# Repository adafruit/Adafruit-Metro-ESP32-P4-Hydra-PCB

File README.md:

# Adafruit-Metro-ESP32-P4-Hydra-PCB
PCB files for the Adafruit Metro ESP32-P4 Hydra - with 16 MB PSRAM - v1 Chipset

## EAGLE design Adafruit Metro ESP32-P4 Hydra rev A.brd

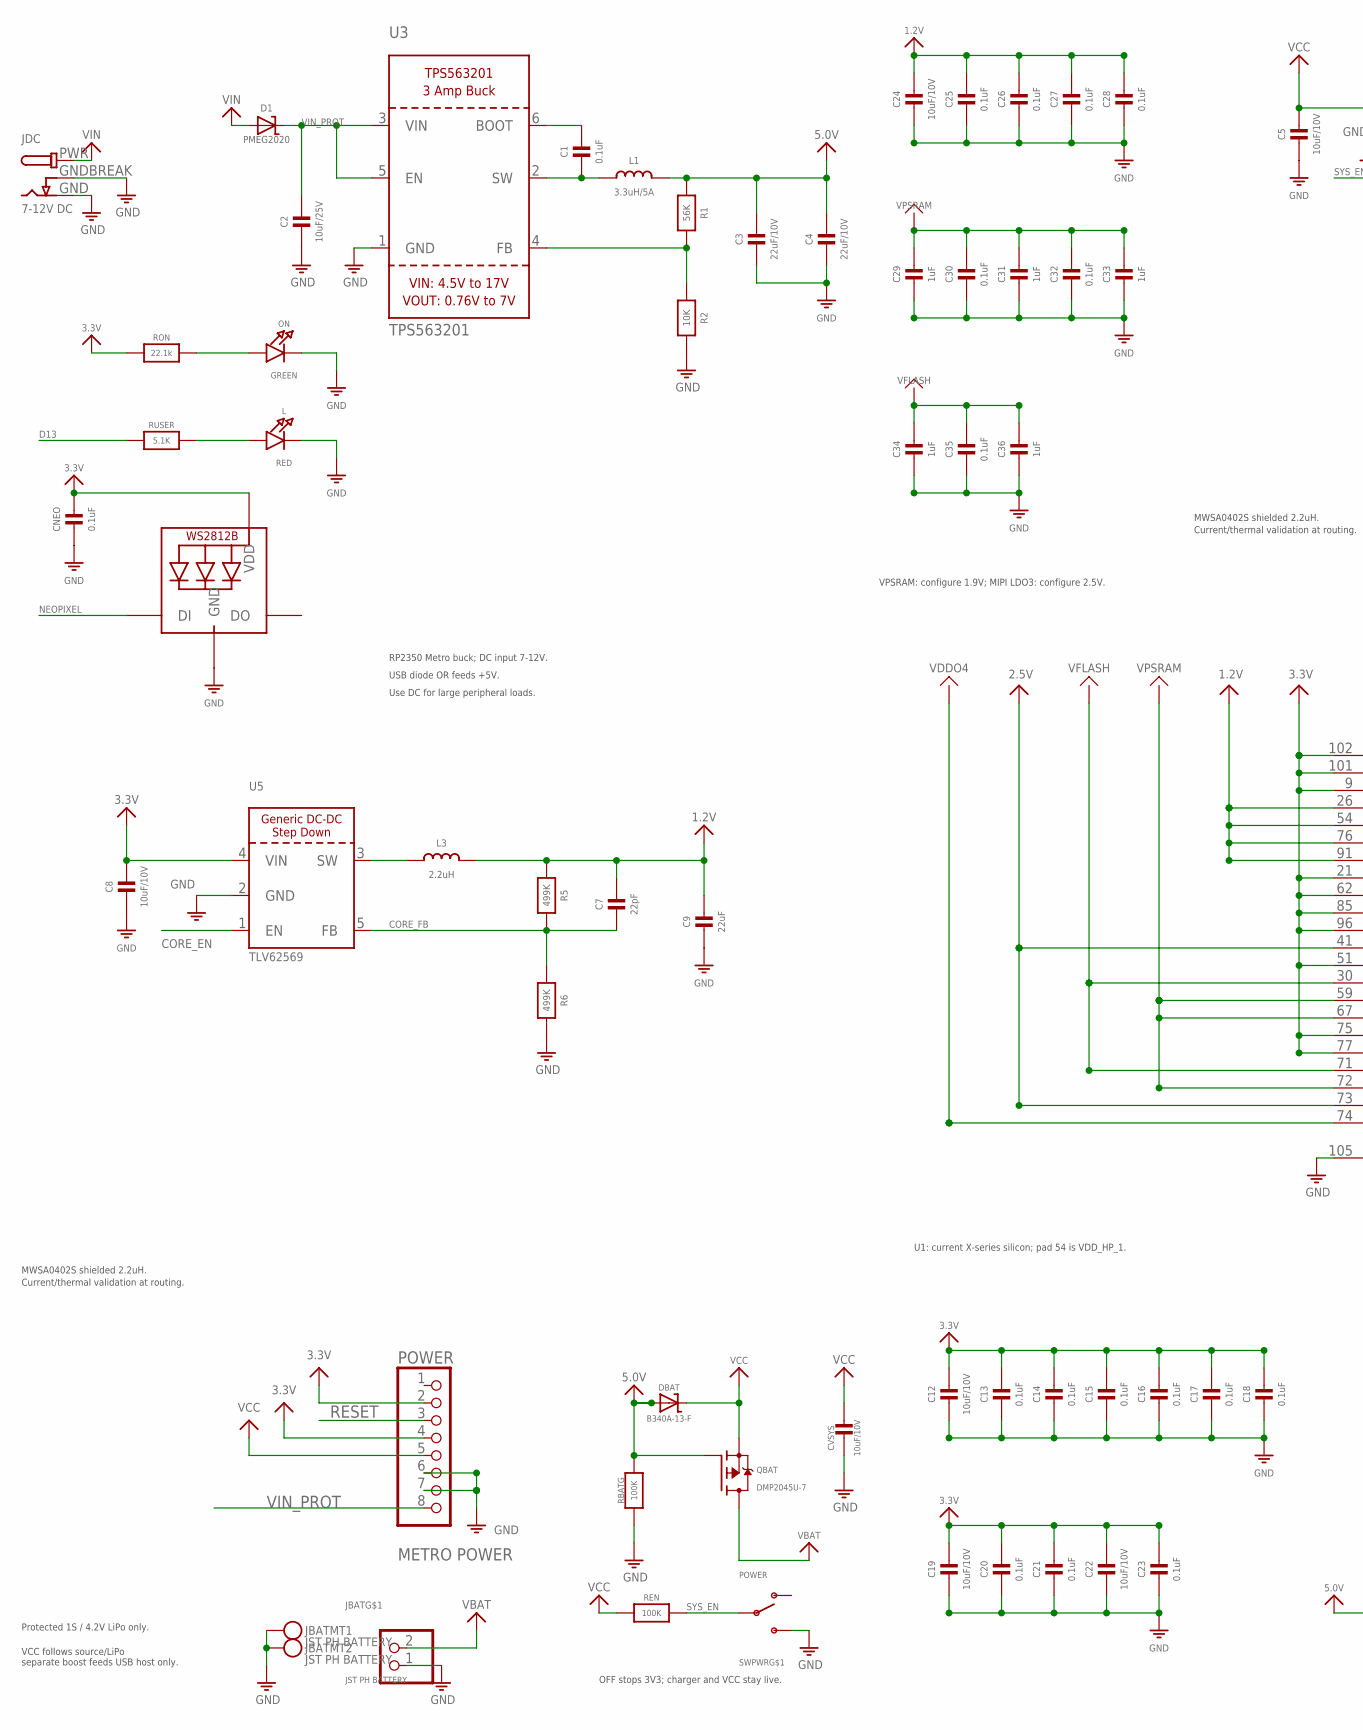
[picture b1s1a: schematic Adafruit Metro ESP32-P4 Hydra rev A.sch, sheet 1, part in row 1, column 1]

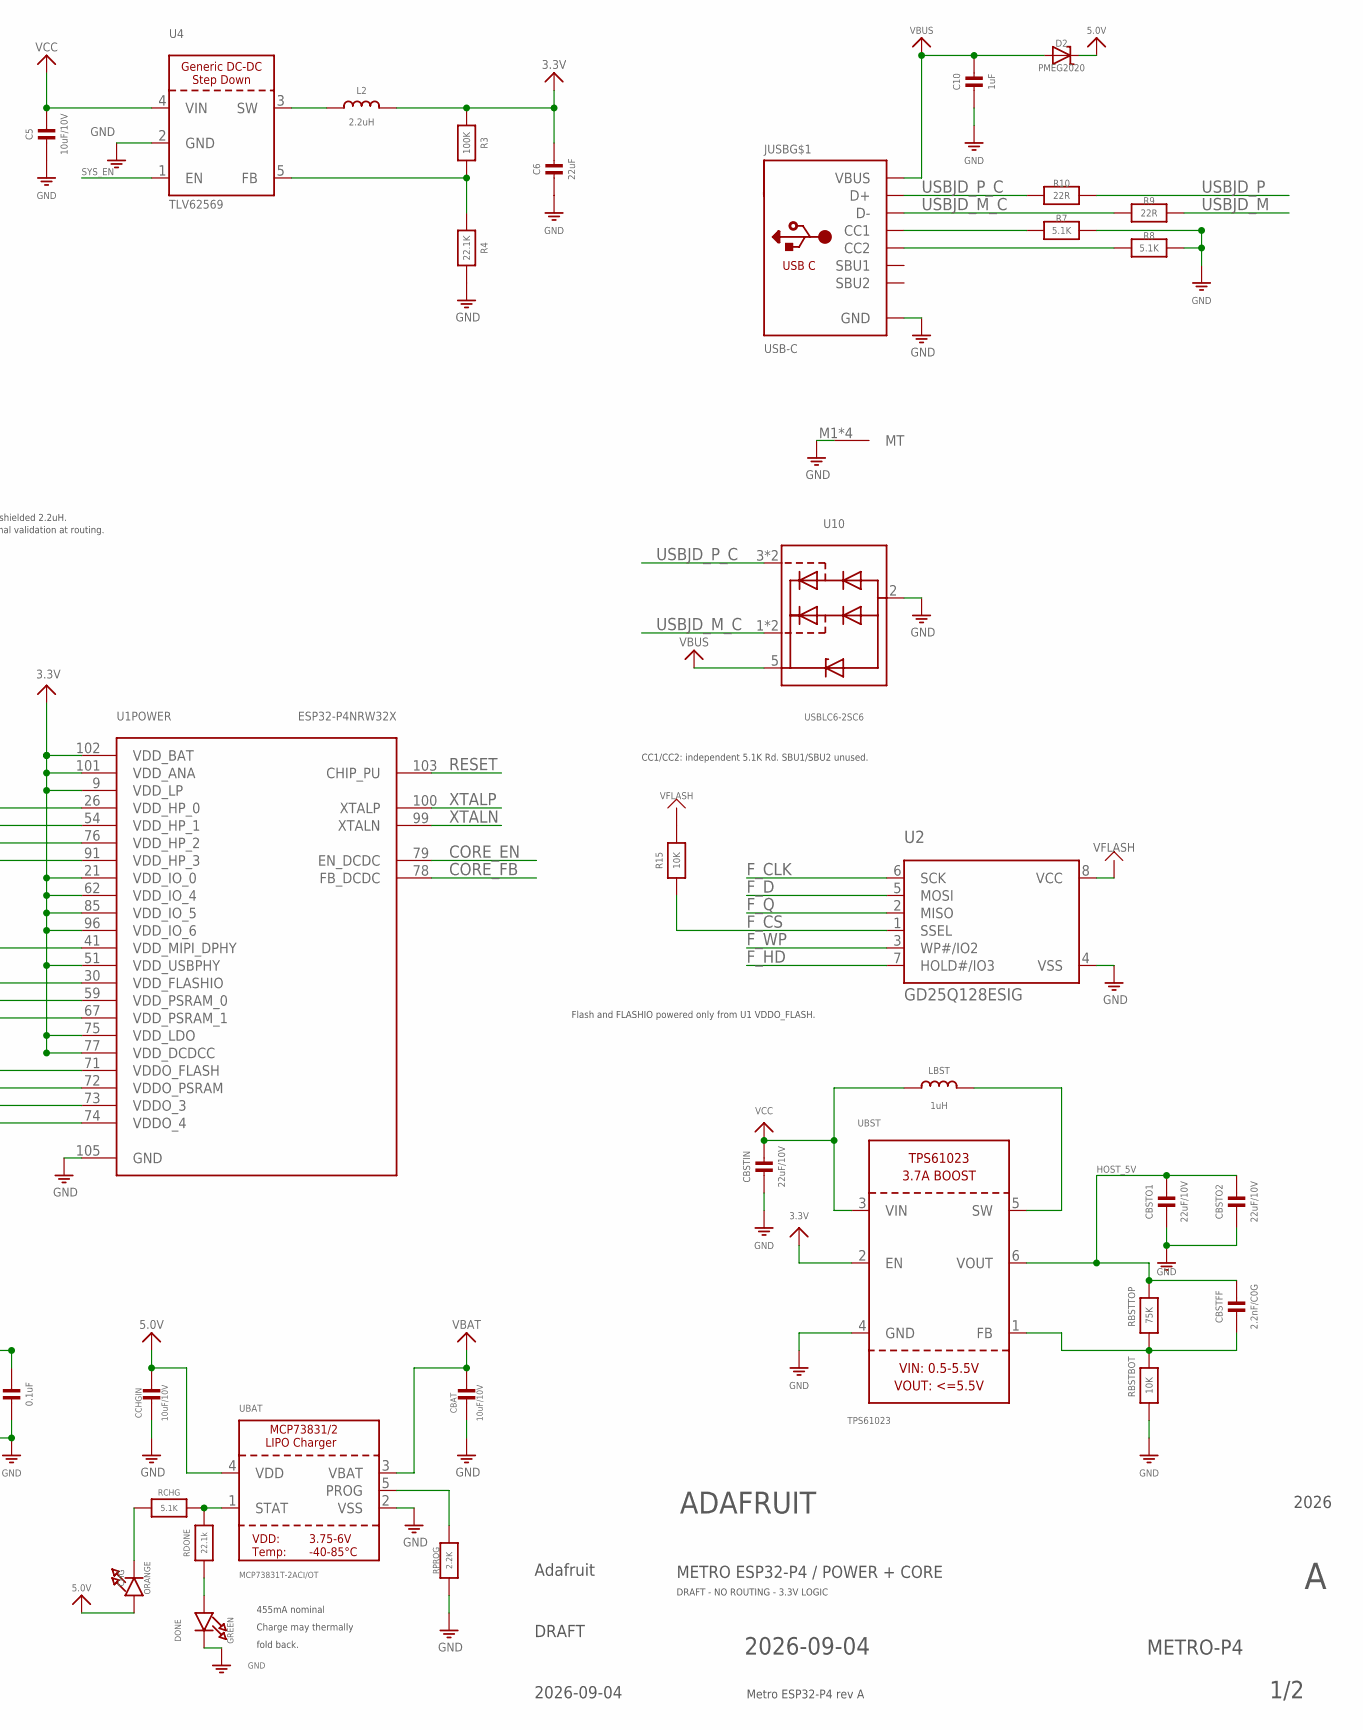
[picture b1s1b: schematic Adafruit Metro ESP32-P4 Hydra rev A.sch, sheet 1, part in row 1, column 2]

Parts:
C1, C13, C14, C15, C16, C17, C18, C20, C21, C23, C25, C26, C27, C28, C30, C32, C35: 0.1uF; _0402NO
C2: 10uF/25V; 0805-NO
C3, C4: 22uF/10V; 0805-NO
C5, C8, C12, C19, C22, C24: 10uF/10V; 0805-NO
C6, C9: 22uF; 0805-NO
C7: 22pF; _0402NO
C10, C29, C31, C33, C34, C36: 1uF; 0603-NO
CBAT: 10uF/10V; 0805-NO
CBSTFF: 2.2nF/C0G; _0402NO; MPN GRM1555C1H222GA01D; LCSC C2987940
CBSTIN: 22uF/10V; 0805-NO; MPN CL21A226MPQNNNE; LCSC C29277
CBSTO1, CBSTO2: 22uF/10V; 0805-NO; MPN CL21A226MPQNNNE; LCSC C29277
CCHGIN: 10uF/10V; 0805-NO
CHG: ORANGE; CHIPLED_0603_NOOUTLINE
CNEO: 0.1uF; _0402NO
CVSYS: 10uF/10V; 0805-NO
D1, D2: PMEG2020; SOD-323
DBAT: B340A-13-F; SMADIODE; MPN B340A-13-F
DONE: GREEN; CHIPLED_0603_NOOUTLINE
HYDRA_ART: METRO-P4-HYDRA; METRO-P4-HYDRA-68.58X53.34
JBAT: JST PH BATTERY; JSTPH2_BATT
JDC: 7-12V DC; DCJACK_2MM_PTH
JUSB: USB-C; USB_C_CUSB31-CFM2AX-01-X
L: RED; CHIPLED_0603_NOOUTLINE
L1: 3.3uH/5A; INDUCTOR_0603S
L2, L3: 2.2uH; INDUCTOR_SUNLORD_MWSA0402S; MPN MWSA0402S-2R2MT; LCSC C408335
LBST: 1uH; INDUCTOR_5045_SMALLTABS
LED1: WS2812B_3535FULL; LED3535_FULLPADS
ON: GREEN; CHIPLED_0603_NOOUTLINE
POWER: METRO POWER; 1X08_OVALWAVE
QBAT: DMP2045U-7; SOT23-R; MPN DMP2045U-7
R1: 56K; _0402NO
R2, R15: 10K; _0402NO
R3: 100K; _0402NO
R4: 22.1K; _0402NO
R5, R6: 499K; _0402NO
R7, R8: 5.1K; _0402NO
R9, R10: 22R; _0402NO
RBATG: 100K; _0402NO
RBSTBOT: 10K; _0402NO
RBSTTOP: 75K; _0402NO
RCHG: 5.1K; _0402NO
RDONE: 22.1k; _0402NO
REN: 100K; _0402NO
RON: 22.1k; _0402NO
RPROG: 2.2K; _0402NO
RUSER: 5.1K; _0402NO
SWPWR: POWER; SPDT_SMT_SSSS811101
U1: ESP32-P4NRW32X; QFN104_10X10_P035_EP76; MPN ESP32-P4NRW32X; LCSC C9900140808
U2: GD25Q128ESIG; SOIC8_208MIL; MPN GD25Q128ESIG
U3: TPS563201; SOT23-6; MPN TPS563201DDCR
U4, U5: TLV62569; SOT23-5; MPN TLV62569DBVR
U10: USBLC6-2SC6; SOT23_6L_ST
UBAT: MCP73831T-2ACI/OT; SOT23-5
UBST: TPS61023; SOT563; MPN TPS61023DRLR; LCSC C919459

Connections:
1.2V: C7.1, C9.1, C24.1, C25.1, C26.1, C27.1, C28.1, L3.P$2 (2), R5.1, U1.26 (VDD_HP_0), U1.54 (VDD_HP_1), U1.76 (VDD_HP_2), U1.91 (VDD_HP_3)
2.5V: U1.41 (VDD_MIPI_DPHY), U1.73 (VDDO_3); also elsewhere on the board
3.3V: C6.1, C8.1, C12.1, C13.1, C14.1, C15.1, C16.1, C17.1, C18.1, C19.1, C20.1, C21.1, C22.1, C23.1, CNEO.1, L2.P$2 (2), LED1.2 (VDD), POWER.2, POWER.4, R3.1, RON.1, U1.9 (VDD_LP), U1.21 (VDD_IO_0), U1.51 (VDD_USBPHY), U1.62 (VDD_IO_4), U1.75 (VDD_LDO), U1.77 (VDD_DCDCC), U1.85 (VDD_IO_5), U1.96 (VDD_IO_6), U1.101 (VDD_ANA), U1.102 (VDD_BAT), U5.4 (VIN), UBST.2 (EN); also elsewhere on the board
5.0V: C3.1, C4.1, CCHGIN.1, CHG.A, D2.C, DBAT.A, L1.P$2 (2), QBAT.1 (G), R1.1, RBATG.1, UBAT.4 (VDD)
BAT_LED: CHG.C, RCHG.1
BAT_PROG: RPROG.1, UBAT.5 (PROG)
BAT_STAT: RCHG.2, RDONE.1, UBAT.1 (STAT)
BST_FB: CBSTFF.2, RBSTBOT.1, RBSTTOP.2, UBST.1 (FB)
BST_SW: LBST.2, UBST.5 (SW)
BUCK5_BST: C1.1, U3.6 (BOOT)
BUCK5_FB: R1.2, R2.1, U3.4 (FB)
BUCK5_SW: C1.2, L1.P$1 (1), U3.2 (SW)
CORE_EN: U1.79 (EN_DCDC), U5.1 (EN)
CORE_FB: C7.2, R5.2, R6.1, U1.78 (FB_DCDC), U5.5 (FB)
D13: RUSER.1; also elsewhere on the board
DONE_LED: DONE.A, RDONE.2
F_CLK: U2.6 (SCK); also elsewhere on the board
F_CS: R15.2, U2.1 (SSEL); also elsewhere on the board
F_D: U2.5 (MOSI); also elsewhere on the board
F_HD: U2.7 (HOLD#/IO3); also elsewhere on the board
F_Q: U2.2 (MISO); also elsewhere on the board
F_WP: U2.3 (WP#/IO2); also elsewhere on the board
GND: C2.2, C3.2, C4.2, C5.2, C6.2, C8.2, C9.2, C10.2, C12.2, C13.2, C14.2, C15.2, C16.2, C17.2, C18.2, C19.2, C20.2, C21.2, C22.2, C23.2, C24.2, C25.2, C26.2, C27.2, C28.2, C29.2, C30.2, C31.2, C32.2, C33.2, C34.2, C35.2, C36.2, CBAT.2, CBSTIN.2, CBSTO1.2, CBSTO2.2, CCHGIN.2, CNEO.2, CVSYS.2, DONE.C, JBAT.1, JBAT.NC1, JBAT.NC2, JDC.GND, JDC.GNDBREAK, JUSB.A1B12 (GND), JUSB.B1A12 (GND), JUSB.M1 (MT), JUSB.M2 (MT), JUSB.M3 (MT), JUSB.M4 (MT), L.C, LED1.4 (GND), ON.C, POWER.6, POWER.7, R2.2, R4.2, R6.2, R7.2, R8.2, RBATG.2, RBSTBOT.2, RPROG.2, SWPWR.C (S), U1.105 (GND), U2.4 (VSS), U3.1 (GND), U4.2 (GND), U5.2 (GND), U10.2 (GND), UBAT.2 (VSS), UBST.4 (GND); also elsewhere on the board
HOST_5V: CBSTFF.1, CBSTO1.1, CBSTO2.1, RBSTTOP.1, UBST.6 (VOUT); also elsewhere on the board
JUSBCC1: JUSB.A5 (CC1), R7.1
JUSBCC2: JUSB.B5 (CC2), R8.1
LED_ON: ON.A, RON.2
LED_USER: L.A, RUSER.2
NEOPIXEL: LED1.1 (DI); also elsewhere on the board
RESET: POWER.3, U1.103 (CHIP_PU); also elsewhere on the board
SYS_EN: REN.2, SWPWR.B, U4.1 (EN)
U4_FB: R3.2, R4.1, U4.5 (FB)
U4_SW: L2.P$1 (1), U4.3 (SW)
U5_SW: L3.P$1 (1), U5.3 (SW)
USBJD_M: R9.2; also elsewhere on the board
USBJD_M_C: JUSB.A7 (D-), JUSB.B7 (D-), R9.1, U10.1 (IO1), U10.6 (IO1)
USBJD_P: R10.2; also elsewhere on the board
USBJD_P_C: JUSB.A6 (D+), JUSB.B6 (D+), R10.1, U10.3 (IO2), U10.4 (IO2)
VBAT: CBAT.1, JBAT.2, QBAT.3 (D), UBAT.3 (VBAT); also elsewhere on the board
VBUS: C10.1, D2.A, JUSB.A4B9 (VBUS), JUSB.B4A9 (VBUS), U10.5 (VCC)
VCC: C5.1, CBSTIN.1, CVSYS.1, DBAT.C, LBST.1, POWER.5, QBAT.2 (S), REN.1, U4.4 (VIN), UBST.3 (VIN); also elsewhere on the board
VDDO4: U1.74 (VDDO_4); also elsewhere on the board
VFLASH: C34.1, C35.1, C36.1, R15.1, U1.30 (VDD_FLASHIO), U1.71 (VDDO_FLASH), U2.8 (VCC)
VIN: D1.A, JDC.PWR
VIN_PROT: C2.1, D1.C, POWER.8, U3.3 (VIN), U3.5 (EN)
VPSRAM: C29.1, C30.1, C31.1, C32.1, C33.1, U1.59 (VDD_PSRAM_0), U1.67 (VDD_PSRAM_1), U1.72 (VDDO_PSRAM)
XTALN: U1.99 (XTALN); also elsewhere on the board
XTALP: U1.100 (XTALP); also elsewhere on the board

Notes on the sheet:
1/2
Metro ESP32-P4 rev A
2026-09-04
2026
ADAFRUIT
Adafruit
DRAFT
METRO-P4
METRO ESP32-P4 / POWER + CORE
DRAFT - NO ROUTING - 3.3V LOGIC
RP2350 Metro buck; DC input 7-12V.
USB diode OR feeds +5V.
MWSA0402S shielded 2.2uH.
Current/thermal validation at routing.
CC1/CC2: independent 5.1K Rd. SBU1/SBU2 unused.
U1: current X-series silicon; pad 54 is VDD_HP_1.
VPSRAM: configure 1.9V; MIPI LDO3: configure 2.5V.
Flash and FLASHIO powered only from U1 VDDO_FLASH.
455mA nominal
OFF stops 3V3; charger and VCC stay live.
Protected 1S / 4.2V LiPo only.
VCC follows source/LiPo separate boost feeds USB host only.
Use DC for large peripheral loads.
Charge may thermally
fold back.

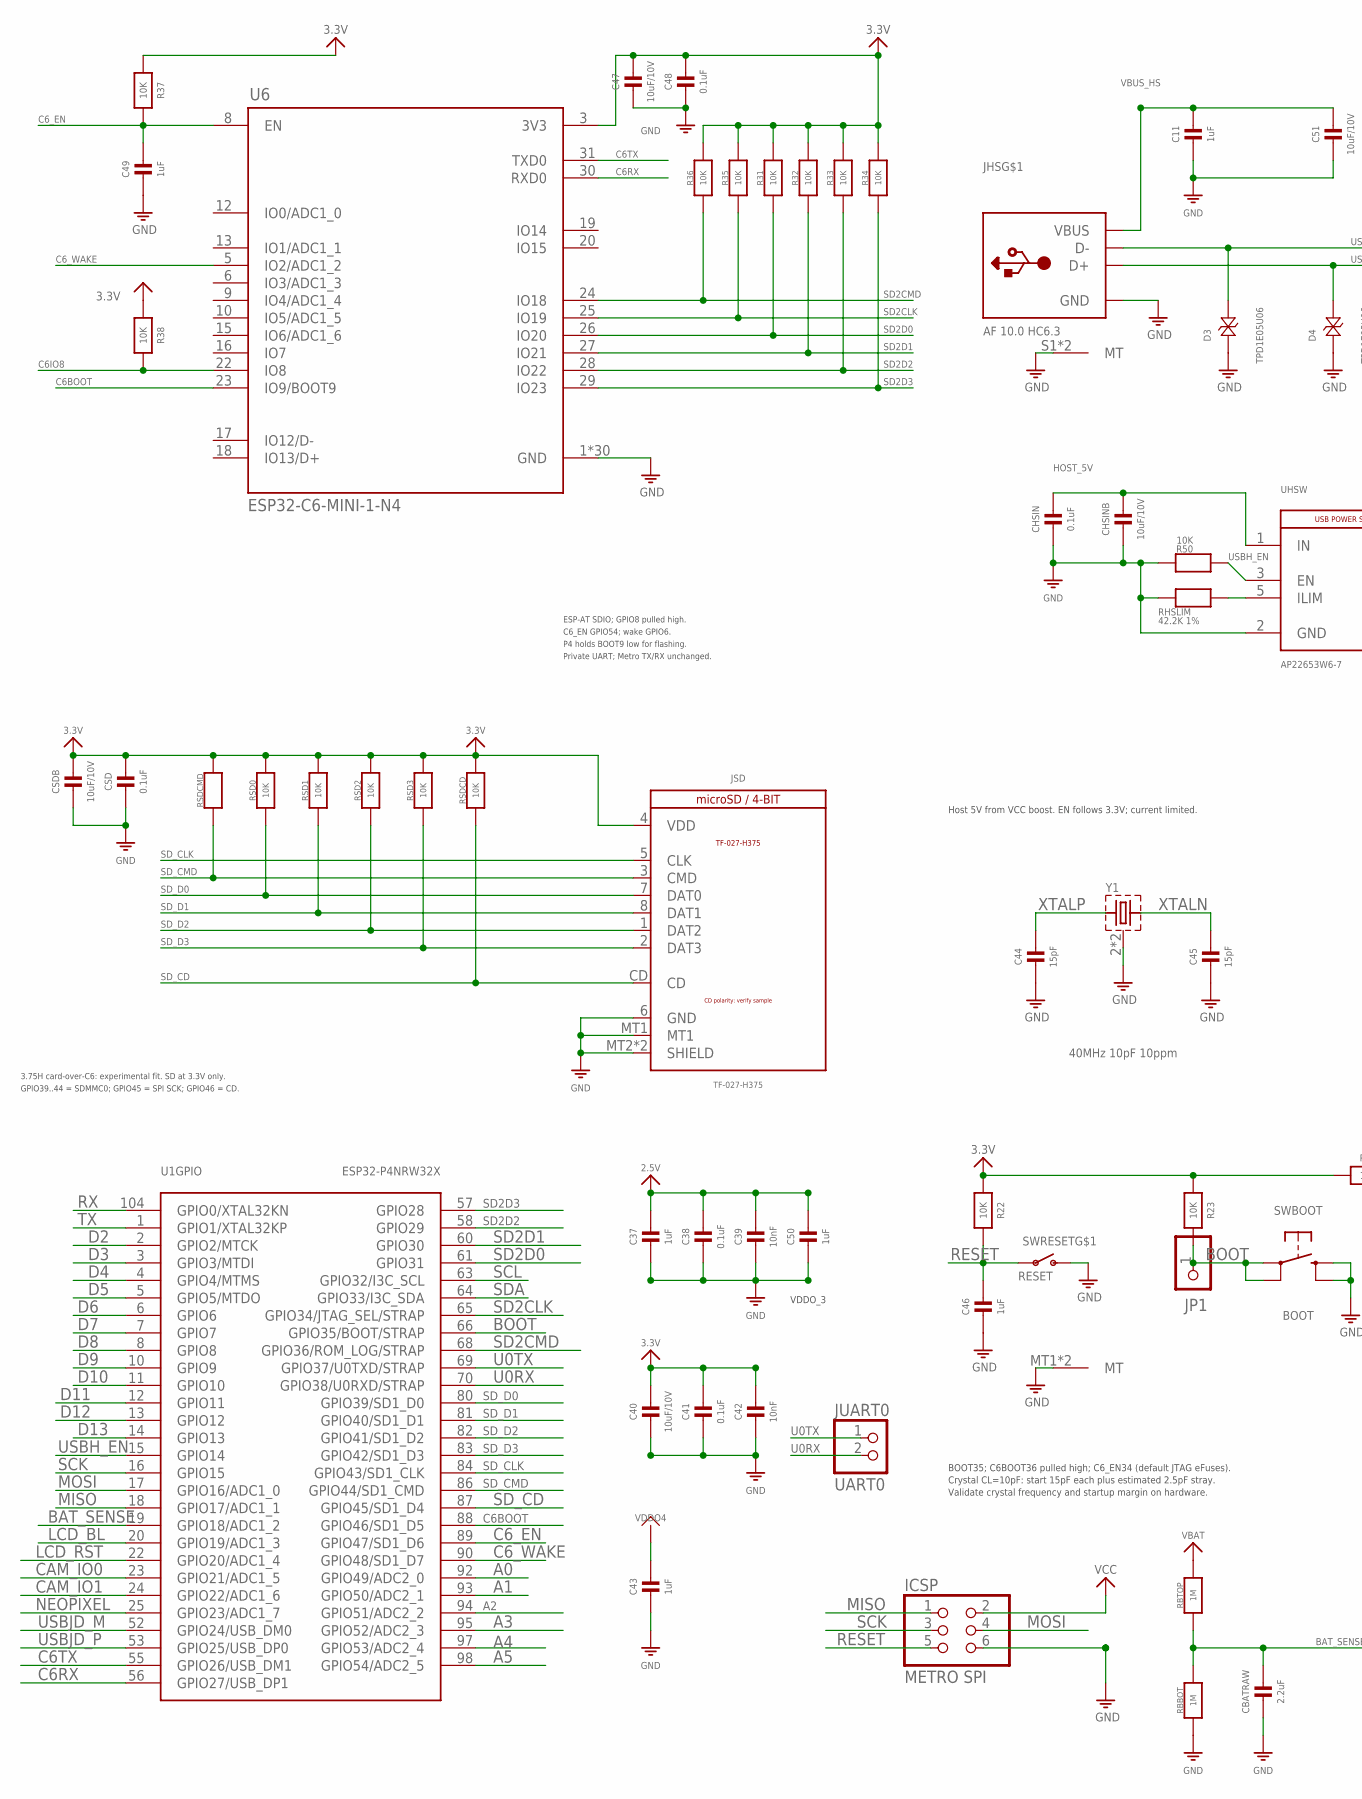
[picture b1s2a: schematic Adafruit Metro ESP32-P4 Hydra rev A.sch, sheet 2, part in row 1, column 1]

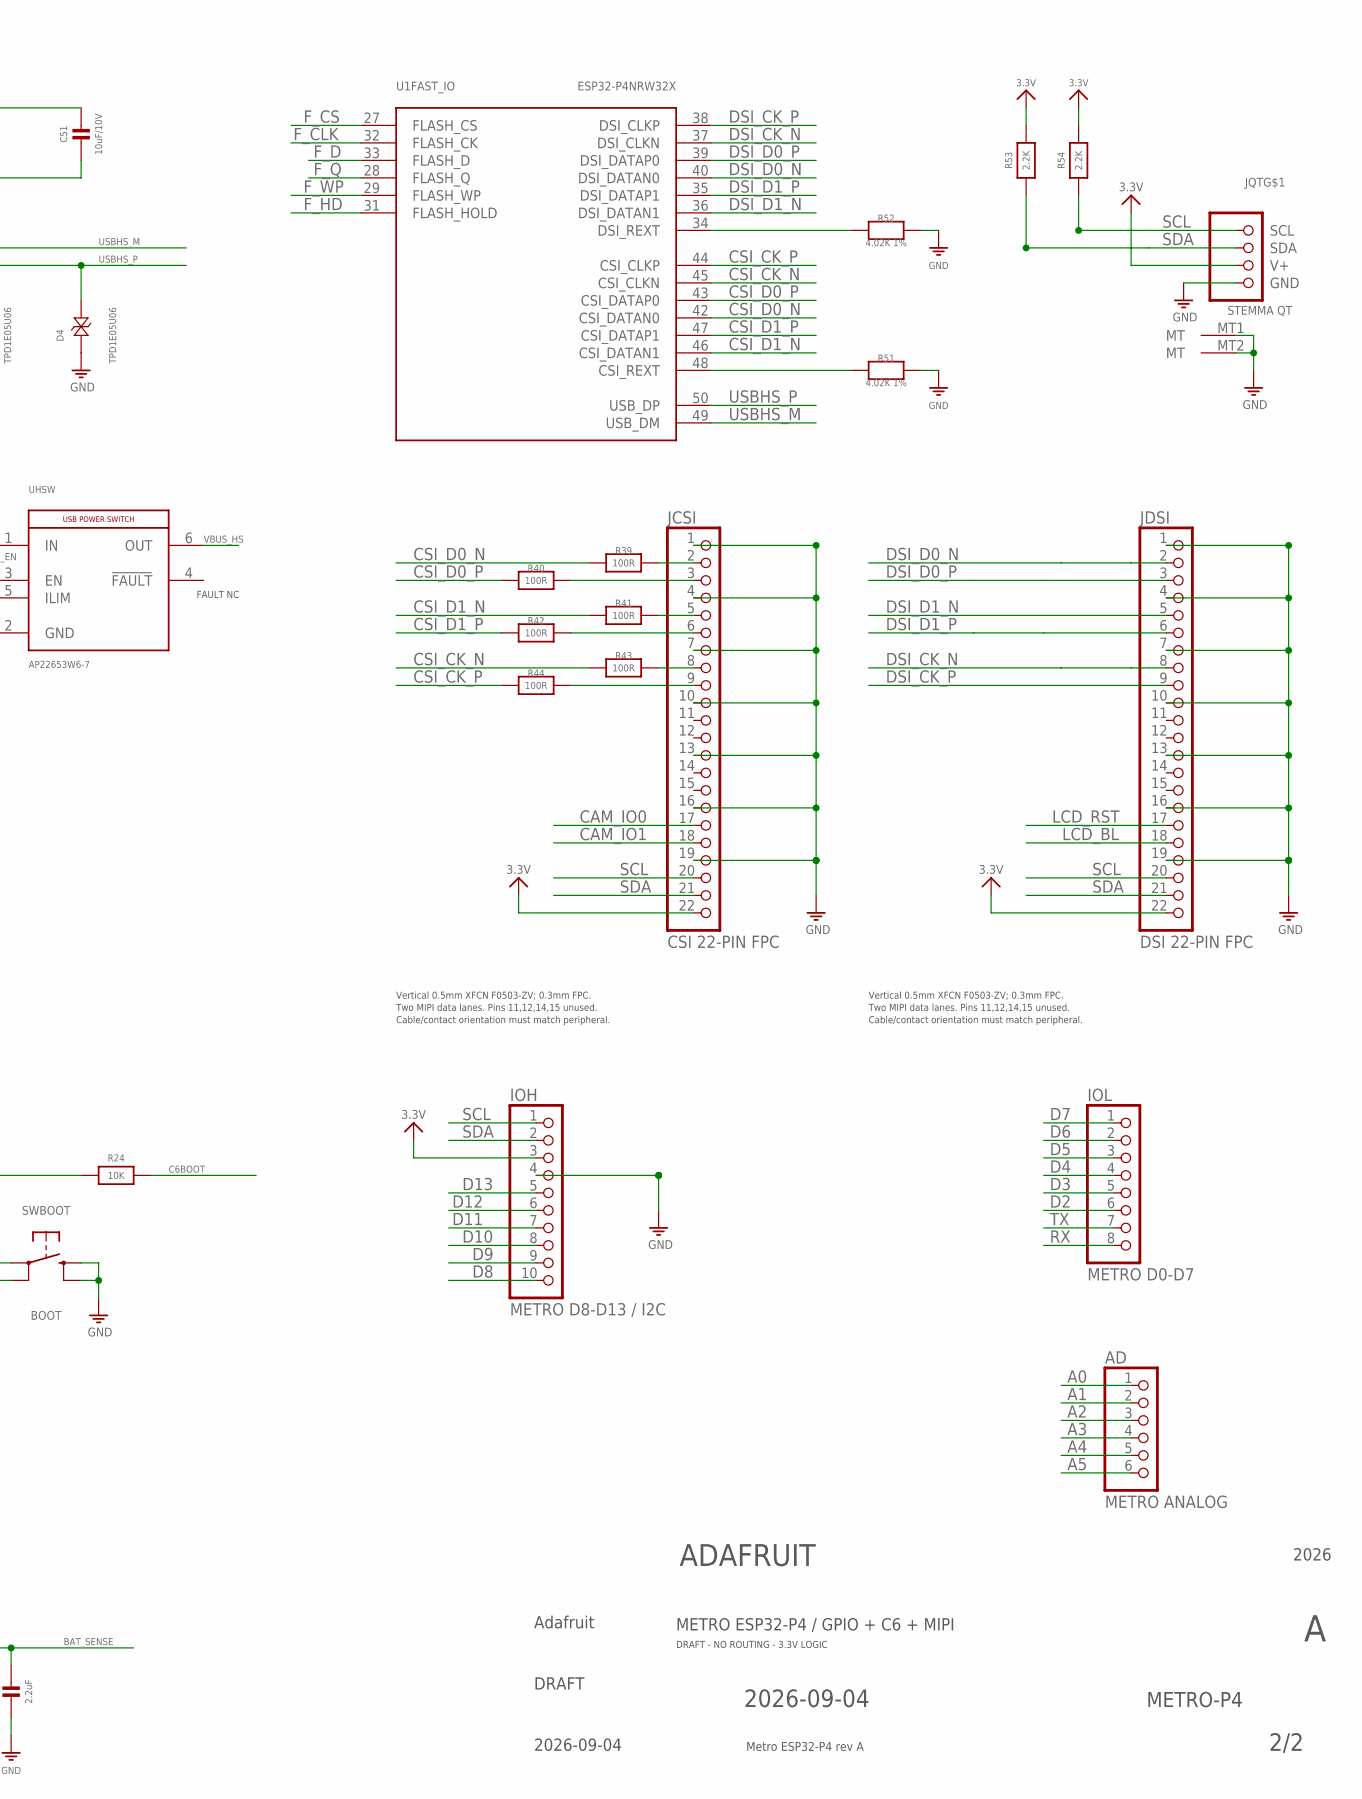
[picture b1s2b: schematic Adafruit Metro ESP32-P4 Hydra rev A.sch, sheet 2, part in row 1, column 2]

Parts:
AD: METRO ANALOG; 1X06_OVALWAVE
C11, C37, C43, C46, C49, C50: 1uF; 0603-NO
C38, C41, C48: 0.1uF; _0402NO
C39, C42: 10nF; _0402NO
C40, C47, C51: 10uF/10V; 0805-NO
C44, C45: 15pF; _0402NO
CBATRAW: 2.2uF; 0805-NO
CHSIN: 0.1uF; _0402NO
CHSINB: 10uF/10V; 0805-NO
CSD: 0.1uF; _0402NO
CSDB: 10uF/10V; 0805-NO
D3, D4: TPD1E05U06; SOD-523; MPN TPD1E05U06DYAR
ICSP: METRO SPI; 2X03_ROUND_70MIL
IOH: METRO D8-D13 / I2C; 1X10_OVALWAVE
IOL: METRO D0-D7; 1X08_OVALWAVE
JCSI: CSI 22-PIN FPC; FPC_22PIN_0.5MM_VERT_F0503_ZV; MPN F0503-ZV-22-20T-R; LCSC C481245
JDSI: DSI 22-PIN FPC; FPC_22PIN_0.5MM_VERT_F0503_ZV; MPN F0503-ZV-22-20T-R; LCSC C481245
JHS: AF 10.0 HC6.3; USB_TYPE_A_THM_SHORT; MPN AF 10.0 HC6.3; LCSC C456017
JP1: HEADER-1X1ROUND; 1X01_ROUND
JQT: STEMMA QT; JST_SH4
JSD: TF-027-H375; HANBO_TF_027_H375; MPN TF-027-H375; LCSC C22374618
JUART0: UART0; 1X02_ROUND
R22, R23, R24, R31, R32, R33, R34, R35, R36, R37, R38, R50: 10K; _0402NO
R39, R40, R41, R42, R43, R44: 100R; _0402NO
R51, R52: 4.02K 1%; _0402NO
R53, R54: 2.2K; _0402NO
RBBOT: 1M; _0402NO
RBTOP: 1M; _0402NO
RHSLIM: 42.2K 1%; _0402NO
RSD0, RSD1, RSD2, RSD3: 10K; _0402NO
RSDCD: 10K; _0402NO
RSDCMD: 10K; _0402NO
SWBOOT: BOOT; BTN_RKB2_4.6X2.8; MPN GT-TC048D-H025-L1; LCSC C843674
SWRESET: RESET; SPST_TACTILE_RA
U1: ESP32-P4NRW32X; QFN104_10X10_P035_EP76; MPN ESP32-P4NRW32X; LCSC C9900140808
U6: ESP32-C6-MINI-1-N4; ESP32-PICO-MINI; MPN ESP32-C6-MINI-1-N4
UHSW: AP22653W6-7; SOT26_TYPE_A1_DIODES; MPN AP22653W6-7; LCSC C2158037
Y1: 40MHz 10pF 10ppm; CRYSTAL_2X1.6; MPN ECS-400-10-37B-CKY-TR3

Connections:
2.5V: C37.1, C38.1, C39.1, C50.1; also elsewhere on the board
3.3V: C40.1, C41.1, C42.1, C47.1, C48.1, CSD.1, CSDB.1, IOH.3, JCSI.22, JDSI.22, JQT.2 (V+), JSD.4 (VDD), R22.1, R23.1, R24.1, R31.1, R32.1, R33.1, R34.1, R35.1, R36.1, R37.1, R38.1, R53.1, R54.1, RSD0.1, RSD1.1, RSD2.1, RSD3.1, RSDCD.1, RSDCMD.1, U6.3 (3V3); also elsewhere on the board
A0: AD.1, U1.92 (GPIO49/ADC2_0)
A1: AD.2, U1.93 (GPIO50/ADC2_1)
A2: AD.3, U1.94 (GPIO51/ADC2_2)
A3: AD.4, U1.95 (GPIO52/ADC2_3)
A4: AD.5, U1.97 (GPIO53/ADC2_4)
A5: AD.6, U1.98 (GPIO54/ADC2_5)
BAT_SENSE: CBATRAW.1, RBBOT.1, RBTOP.2, U1.19 (GPIO18/ADC1_2)
BOOT: JP1.1, R23.2, SWBOOT.A, SWBOOT.A' (P1), U1.66 (GPIO35/BOOT/STRAP)
C6BOOT: R24.2, U1.88 (GPIO46/SD1_D5), U6.23 (IO9/BOOT9)
C6IO8: R38.2, U6.22 (IO8)
C6RX: U1.56 (GPIO27/USB_DP1), U6.30 (RXD0)
C6TX: U1.55 (GPIO26/USB_DM1), U6.31 (TXD0)
C6_EN: C49.1, R37.2, U1.89 (GPIO47/SD1_D6), U6.8 (EN)
C6_WAKE: U1.90 (GPIO48/SD1_D7), U6.5 (IO2/ADC1_2)
CAM_IO0: JCSI.17, U1.23 (GPIO21/ADC1_5)
CAM_IO1: JCSI.18, U1.24 (GPIO22/ADC1_6)
CSI_CK_C_N: JCSI.8, R43.2
CSI_CK_C_P: JCSI.9, R44.2
CSI_CK_N: R43.1, U1.45 (CSI_CLKN)
CSI_CK_P: R44.1, U1.44 (CSI_CLKP)
CSI_D0_C_N: JCSI.2, R39.2
CSI_D0_C_P: JCSI.3, R40.2
CSI_D0_N: R39.1, U1.42 (CSI_DATAN0)
CSI_D0_P: R40.1, U1.43 (CSI_DATAP0)
CSI_D1_C_N: JCSI.5, R41.2
CSI_D1_C_P: JCSI.6, R42.2
CSI_D1_N: R41.1, U1.46 (CSI_DATAN1)
CSI_D1_P: R42.1, U1.47 (CSI_DATAP1)
CSI_EXT: R51.1, U1.48 (CSI_REXT)
D2: IOL.6, U1.2 (GPIO2/MTCK)
D3: IOL.5, U1.3 (GPIO3/MTDI)
D4: IOL.4, U1.4 (GPIO4/MTMS)
D5: IOL.3, U1.5 (GPIO5/MTDO)
D6: IOL.2, U1.6 (GPIO6)
D7: IOL.1, U1.7 (GPIO7)
D8: IOH.10, U1.8 (GPIO8)
D9: IOH.9, U1.10 (GPIO9)
D10: IOH.8, U1.11 (GPIO10)
D11: IOH.7, U1.12 (GPIO11)
D12: IOH.6, U1.13 (GPIO12)
D13: IOH.5, U1.14 (GPIO13); also elsewhere on the board
DSI_CK_N: JDSI.8, U1.37 (DSI_CLKN)
DSI_CK_P: JDSI.9, U1.38 (DSI_CLKP)
DSI_D0_N: JDSI.2, U1.40 (DSI_DATAN0)
DSI_D0_P: JDSI.3, U1.39 (DSI_DATAP0)
DSI_D1_N: JDSI.5, U1.36 (DSI_DATAN1)
DSI_D1_P: JDSI.6, U1.35 (DSI_DATAP1)
DSI_EXT: R52.1, U1.34 (DSI_REXT)
F_CLK: U1.32 (FLASH_CK); also elsewhere on the board
F_CS: U1.27 (FLASH_CS); also elsewhere on the board
F_D: U1.33 (FLASH_D); also elsewhere on the board
F_HD: U1.31 (FLASH_HOLD); also elsewhere on the board
F_Q: U1.28 (FLASH_Q); also elsewhere on the board
F_WP: U1.29 (FLASH_WP); also elsewhere on the board
GND: C11.2, C37.2, C38.2, C39.2, C40.2, C41.2, C42.2, C43.2, C44.2, C45.2, C46.2, C47.2, C48.2, C49.2, C50.2, C51.2, CBATRAW.2, CHSIN.2, CHSINB.2, CSD.2, CSDB.2, D3.A, D4.A, ICSP.6, IOH.4, JCSI.1, JCSI.4, JCSI.7, JCSI.10, JCSI.13, JCSI.16, JCSI.19, JDSI.1, JDSI.4, JDSI.7, JDSI.10, JDSI.13, JDSI.16, JDSI.19, JHS.GND, JHS.S1 (MT), JHS.S2 (MT), JQT.1 (GND), JQT.MT1 (MT), JQT.MT2 (MT), JSD.6 (GND), JSD.MT1, JSD.MT2 (SHIELD), JSD.MT3 (SHIELD), R50.2, R51.2, R52.2, RBBOT.2, RHSLIM.1, SWBOOT.B (S), SWBOOT.B' (S1), SWRESET.2 (S), SWRESET.MT1 (MT), SWRESET.MT2 (MT), U6.1 (GND), U6.2 (GND), U6.11 (GND), U6.14 (GND), U6.36 (GND), U6.37 (GND), U6.38 (GND), U6.39 (GND), U6.40 (GND), U6.41 (GND), U6.42 (GND), U6.43 (GND), U6.44 (GND), U6.45 (GND), U6.46 (GND), U6.47 (GND), U6.48 (GND), U6.49 (GND), U6.50 (GND), U6.51 (GND), U6.52 (GND), U6.53 (GND), U6.54 (GND), U6.55 (GND), U6.56 (GND), U6.57 (GND), U6.58 (GND), U6.59 (GND), U6.60 (GND), U6.61 (GND), UHSW.2 (GND), Y1.2 (GND), Y1.4 (GND); also elsewhere on the board
HOST_5V: CHSIN.1, CHSINB.1, UHSW.1 (IN); also elsewhere on the board
HOST_ILIM: RHSLIM.2, UHSW.5 (ILIM)
LCD_BL: JDSI.18, U1.20 (GPIO19/ADC1_3)
LCD_RST: JDSI.17, U1.22 (GPIO20/ADC1_4)
MISO: ICSP.1, U1.18 (GPIO17/ADC1_1)
MOSI: ICSP.4, U1.17 (GPIO16/ADC1_0)
NEOPIXEL: U1.25 (GPIO23/ADC1_7); also elsewhere on the board
RESET: C46.1, ICSP.5, R22.2, SWRESET.1; also elsewhere on the board
RX: IOL.8, U1.104 (GPIO0/XTAL32KN)
SCK: ICSP.3, U1.16 (GPIO15)
SCL: IOH.1, JCSI.20, JDSI.20, JQT.4 (SCL), R54.2, U1.63 (GPIO32/I3C_SCL)
SD2CLK: R35.2, U1.65 (GPIO34/JTAG_SEL/STRAP), U6.25 (IO19)
SD2CMD: R36.2, U1.68 (GPIO36/ROM_LOG/STRAP), U6.24 (IO18)
SD2D0: R31.2, U1.61 (GPIO31), U6.26 (IO20)
SD2D1: R32.2, U1.60 (GPIO30), U6.27 (IO21)
SD2D2: R33.2, U1.58 (GPIO29), U6.28 (IO22)
SD2D3: R34.2, U1.57 (GPIO28), U6.29 (IO23)
SDA: IOH.2, JCSI.21, JDSI.21, JQT.3 (SDA), R53.2, U1.64 (GPIO33/I3C_SDA)
SD_CD: JSD.CD, RSDCD.2, U1.87 (GPIO45/SD1_D4)
SD_CLK: JSD.5 (CLK), U1.84 (GPIO43/SD1_CLK)
SD_CMD: JSD.3 (CMD), RSDCMD.2, U1.86 (GPIO44/SD1_CMD)
SD_D0: JSD.7 (DAT0), RSD0.2, U1.80 (GPIO39/SD1_D0)
SD_D1: JSD.8 (DAT1), RSD1.2, U1.81 (GPIO40/SD1_D1)
SD_D2: JSD.1 (DAT2), RSD2.2, U1.82 (GPIO41/SD1_D2)
SD_D3: JSD.2 (DAT3), RSD3.2, U1.83 (GPIO42/SD1_D3)
TX: IOL.7, U1.1 (GPIO1/XTAL32KP)
U0RX: JUART0.2, U1.70 (GPIO38/U0RXD/STRAP)
U0TX: JUART0.1, U1.69 (GPIO37/U0TXD/STRAP)
USBHS_M: D3.K (C), JHS.D-, U1.49 (USB_DM)
USBHS_P: D4.K (C), JHS.D+, U1.50 (USB_DP)
USBH_EN: R50.1, U1.15 (GPIO14), UHSW.3 (EN)
USBJD_M: U1.52 (GPIO24/USB_DM0); also elsewhere on the board
USBJD_P: U1.53 (GPIO25/USB_DP0); also elsewhere on the board
VBAT: RBTOP.1; also elsewhere on the board
VBUS_HS: C11.1, C51.1, JHS.VBUS, UHSW.6 (OUT)
VCC: ICSP.2; also elsewhere on the board
VDDO4: C43.1; also elsewhere on the board
XTALN: C45.1, Y1.3 (2); also elsewhere on the board
XTALP: C44.1, Y1.1; also elsewhere on the board

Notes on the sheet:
2/2
Metro ESP32-P4 rev A
2026-09-04
2026
ADAFRUIT
Adafruit
DRAFT
METRO-P4
METRO ESP32-P4 / GPIO + C6 + MIPI
DRAFT - NO ROUTING - 3.3V LOGIC
Host 5V from VCC boost. EN follows 3.3V; current limited.
BOOT35; C6BOOT36 pulled high; C6_EN34 (default JTAG eFuses).
Crystal CL=10pF: start 15pF each plus estimated 2.5pF stray.
Validate crystal frequency and startup margin on hardware.
ESP-AT SDIO; GPIO8 pulled high.
C6_EN GPIO54; wake GPIO6.
P4 holds BOOT9 low for flashing.
Private UART; Metro TX/RX unchanged.
Vertical 0.5mm XFCN F0503-ZV; 0.3mm FPC.
Two MIPI data lanes. Pins 11,12,14,15 unused.
Cable/contact orientation must match peripheral.
VDDO_3
FAULT NC
3.75H card-over-C6: experimental fit. SD at 3.3V only.
GPIO39..44 = SDMMC0; GPIO45 = SPI SCK; GPIO46 = CD.

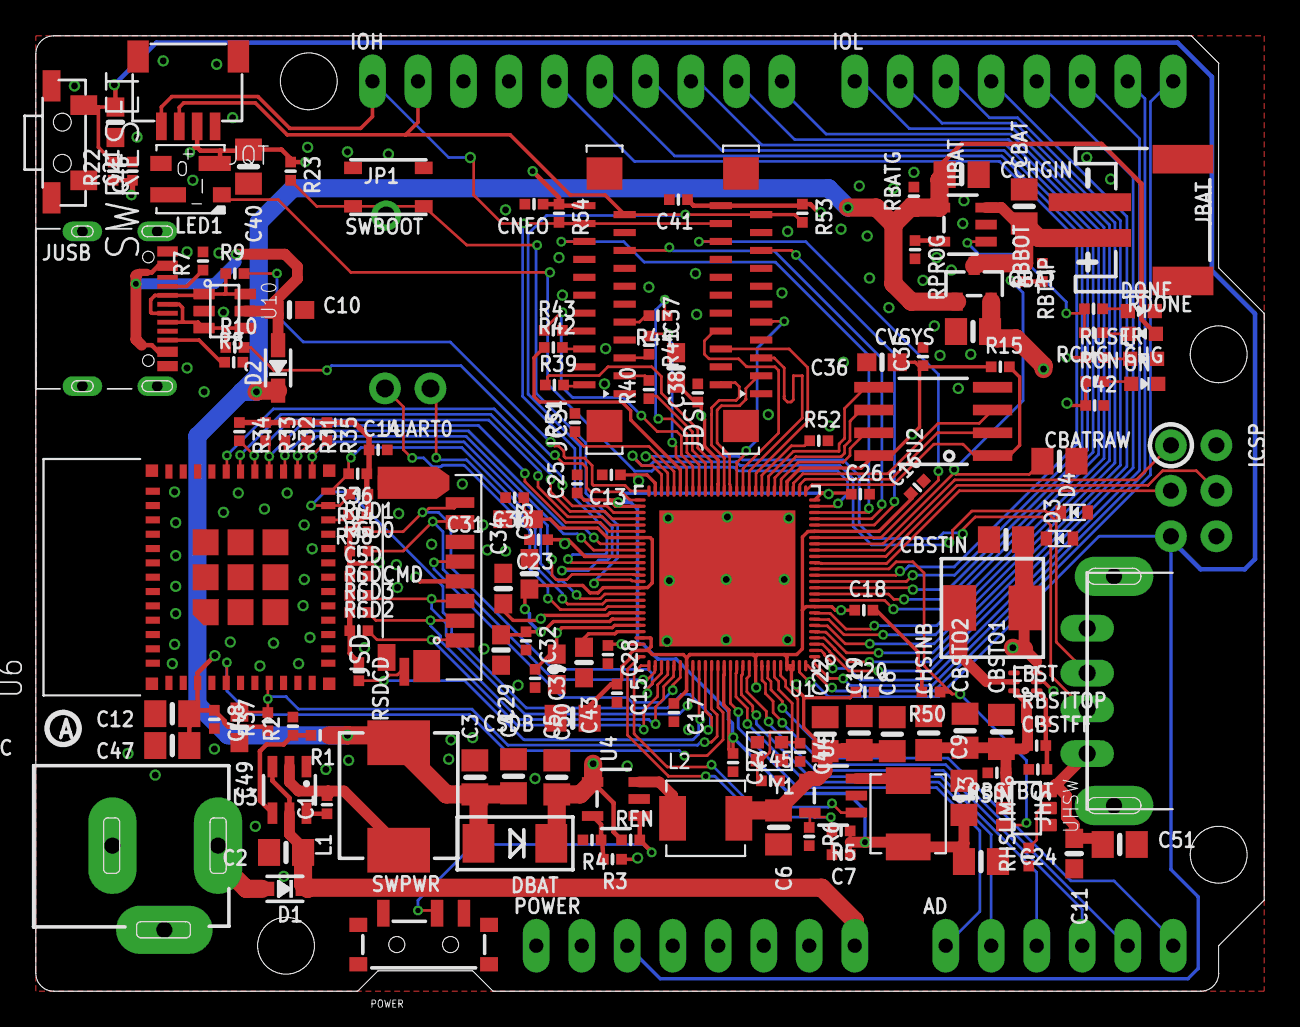
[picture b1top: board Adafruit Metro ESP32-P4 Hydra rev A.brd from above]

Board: 4 copper layers, 68.6 x 53.3 mm, 227 parts (1 on the bottom side), 124 nets.

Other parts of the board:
PLABEL0, PLABEL59: PLABEL0
PLABEL1: PLABEL1
PLABEL2: PLABEL2
PLABEL3, PLABEL5: PLABEL3
PLABEL4, PLABEL31: PLABEL4
PLABEL6, PLABEL28: PLABEL6
PLABEL7, PLABEL8, PLABEL32: PLABEL7
PLABEL9: PLABEL9
PLABEL10: PLABEL10
PLABEL11: PLABEL11
PLABEL12: PLABEL12
PLABEL13: PLABEL13
PLABEL14: PLABEL14
PLABEL15: PLABEL15
PLABEL16: PLABEL16
PLABEL17: PLABEL17
PLABEL18: PLABEL18
PLABEL19: PLABEL19
PLABEL20: PLABEL20
PLABEL21: PLABEL21
PLABEL22: PLABEL22
PLABEL23: PLABEL23
PLABEL24: PLABEL24
PLABEL25: PLABEL25
PLABEL26: PLABEL26
PLABEL27: PLABEL27
PLABEL29: PLABEL29
PLABEL30: PLABEL30
PLABEL33: PLABEL33
PLABEL34: PLABEL34
PLABEL35, PLABEL38: PLABEL35
PLABEL36, PLABEL39: PLABEL36
PLABEL37: PLABEL37
PLABEL40: PLABEL40
PLABEL41: PLABEL41
PLABEL42: PLABEL42
PLABEL43: PLABEL43
PLABEL44: PLABEL44
PLABEL45: PLABEL45
PLABEL46: PLABEL46
PLABEL47: PLABEL47
PLABEL48: PLABEL48
PLABEL49: PLABEL49
PLABEL50: PLABEL50
PLABEL51: PLABEL51
PLABEL52: PLABEL52
PLABEL53: PLABEL53
PLABEL54: PLABEL54
PLABEL55: PLABEL55
PLABEL56: PLABEL56
PLABEL57: PLABEL57
PLABEL58: PLABEL58
PLABEL60: PLABEL60
PLABEL61: PLABEL61
PLABEL62: PLABEL62
PLABEL63: PLABEL63
PLABEL64: PLABEL64
PLABEL65: PLABEL65
U$1: PCBFEAT-REV-040

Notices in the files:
parts and their libraries:
adafruit_wireless: Footprint geometry cross-checked against Espressif kicad-libraries revision dd76561812ab300351234ba6e0ec1295641796f0 (CC-BY-SA-4.0 with design-output exception).
